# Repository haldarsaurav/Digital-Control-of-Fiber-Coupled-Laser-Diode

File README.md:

# Digital Control of Fiber Coupled Laser Diode

Developing a new digital circuit using a micro-controller to drive Laser (LED1) replacing analog methods of curent control. 

The Existing circuit we are trying to reeplicate digitally: 

Some of our objectives :- 

<ul>
  <li>Controlling the current to a LASER thorugh digital means instead of  analog means (Variable Resistors)</li>
  <li>Reading the current drawn and power of the LASER dynamicvally using INA219 Current Sensor</li>
  <li>Interfacing an LCD to monitor the display the PWM value of micro-controller and the curreent and poweer drawn dynamically</li>
</ul>  

Additional improvent and additions

<ul>
  <li>Adding a temperature sensor to measure the ambient temperature</li>
  <li>Adding a bluetooth transreciever to control the curreent value remotely</li> 
  <li>Developing an app or webpage based GUI application</li>
  <li>Logging all the data recieved and store it on sd card or cloud</li>
  <li>Housing all the electronics in a approprite housing.</li>
</ul>  

## Prototyping the existing circuit

Made the circuit following the schematic to drive the LASER

code snippet of sending increased PWM signals through A9 pin of Arduino 

    void loop() {
         analogWrite(9,100);                                           // Laser diode connected to pin A9
         delay(1000);
         analogWrite(9,150);
         delay(1000);
         analogWrite(9,200);
         delay(1000);
         analogWrite(9,250);
         delay(1000);
         analogWrite(9,0);
         delay(1000);
    }

## Intefaced the LCD to show any required data

Code with LCD initialsed:

    // include the library code:

    #include <LiquidCrystal.h>                                     // initialize the library by associating any needed LCD interface pin

    const int rs = 12, en = 11, d4 = 5, d5 = 4, d6 = 3, d7 = 2;    // with the arduino pin number it is connected to

    LiquidCrystal lcd(rs, en, d4, d5, d6, d7);

    void setup() {                                                 // set up the LCD's number of columns and rows:

    lcd.begin(16, 2);

    }

    void loop() {
     analogWrite(9,100);                                           // Laser diode connected to pin A9
     delay(1000);
     analogWrite(9,150);
     delay(1000);
     analogWrite(9,200);
     delay(1000);
     analogWrite(9,250);
     delay(1000);
     analogWrite(9,0);
     delay(1000);

                                                               // LCD Message
    lcd.print("   HELLO       ");
    lcd.setCursor(0,1);                                        // Set the cursor for the second line( the second 1 after comma sets the cursor at the 2 or lower line).
    lcd.print("      WORLD "); 

    }

## Interfaced the INA219 Current sensor to measure the current value

The vale from the INA219 using the LCD's LED as load :) (As I am doing this project Hochschule, I am quite restricted with parts)

Code for inteerfacing INA219 and measuring the current values

    #include <Wire.h>
    #include <Adafruit_INA219.h>

    Adafruit_INA219 ina219;

    void setup(void) 
    {
      Serial.begin(9600);
      while (!Serial) {
          // will pause Zero, Leonardo, etc until serial console opens
          delay(1);
      }

      uint32_t currentFrequency;

      Serial.println("Hello!");

      if (! ina219.begin()) {
        Serial.println("Failed to find INA219 chip");
        while (1) { delay(10); }
      }

      Serial.println("Measuring voltage and current with INA219 ...");
    }

    void loop(void) 
    {
      float shuntvoltage = 0;
      float busvoltage = 0;
      float current_mA = 0;
      float loadvoltage = 0;
      float power_mW = 0;

      shuntvoltage = ina219.getShuntVoltage_mV();
      busvoltage = ina219.getBusVoltage_V();
      current_mA = ina219.getCurrent_mA();
      power_mW = ina219.getPower_mW();
      loadvoltage = busvoltage + (shuntvoltage / 1000);

      Serial.print("Bus Voltage:   "); Serial.print(busvoltage); Serial.println(" V");
      Serial.print("Shunt Voltage: "); Serial.print(shuntvoltage); Serial.println(" mV");
      Serial.print("Load Voltage:  "); Serial.print(loadvoltage); Serial.println(" V");
      Serial.print("Current:       "); Serial.print(current_mA); Serial.println(" mA");
      Serial.print("Power:         "); Serial.print(power_mW); Serial.println(" mW");
      Serial.println("");

      delay(2000);
    }

Schematic for the entire plan and existing circuits which are already implemented, we can futher make the system more compact using an on-board ATMEGA328 IC.

We plan to use MCP4725 to convert the analog PWM signals from Arduino to digital values then use that to drive a current controlled Op-amp circuit in a voltage followeer mode. 

Some of my simulations :-

and then use a HM10 Blueetooth module to control the system oveer bluetooth remotely.

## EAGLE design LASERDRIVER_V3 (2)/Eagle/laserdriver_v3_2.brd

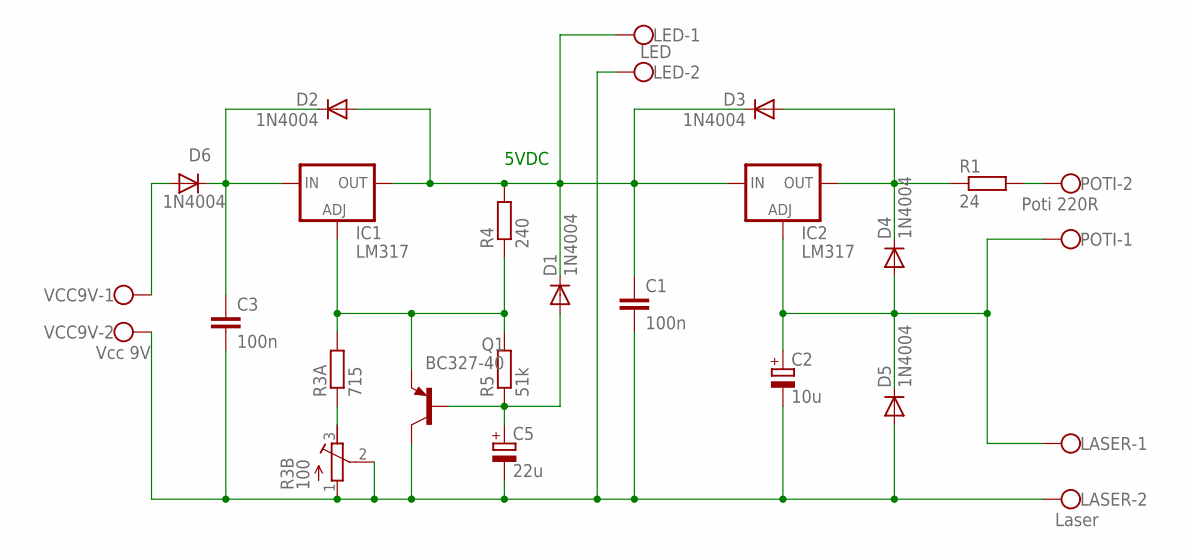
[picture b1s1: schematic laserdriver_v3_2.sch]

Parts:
C1, C3: 100n; C050-024X044
C2: 10u; E2-5
C5: 22u; E2-5
D1, D2, D3, D4, D5, D6: 1N4004; DO41-10
IC1, IC2: LM317; 317TS
LASER: Laser; W237-102
LED: LED; W237-102
POTI: Poti 220R; W237-102
Q1: BC327-40; TO92-EBC
R1: 24; 0207/7
R3A: 715; 0207/7
R3B: 100; RTRIM3296W
R4: 240; 0207/7
R5: 51k; 0207/7
VCC9V: Vcc 9V; W237-102

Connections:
unnamed: C1.1, D1.C, D2.A, D3.C, IC1.2 (OUT), IC2.3 (IN), LED.1, R4.2
unnamed: C2.+, D4.A, D5.C, IC2.1 (ADJ), LASER.1, POTI.1
unnamed: D3.A, D4.C, IC2.2 (OUT), R1.1
unnamed: POTI.2, R1.2
unnamed: C5.+, D1.A, Q1.B, R5.1
unnamed: D6.A, VCC9V.1
unnamed: C3.1, D2.C, D6.C, IC1.3 (IN)
unnamed: R3A.1, R3B.3 (E)
unnamed: C1.2, C2.-, C3.2, C5.-, D5.A, LASER.2, LED.2, Q1.C, R3B.1 (A), R3B.2 (S), VCC9V.2
unnamed: IC1.1 (ADJ), Q1.E, R3A.2, R4.1, R5.2

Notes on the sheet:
5VDC

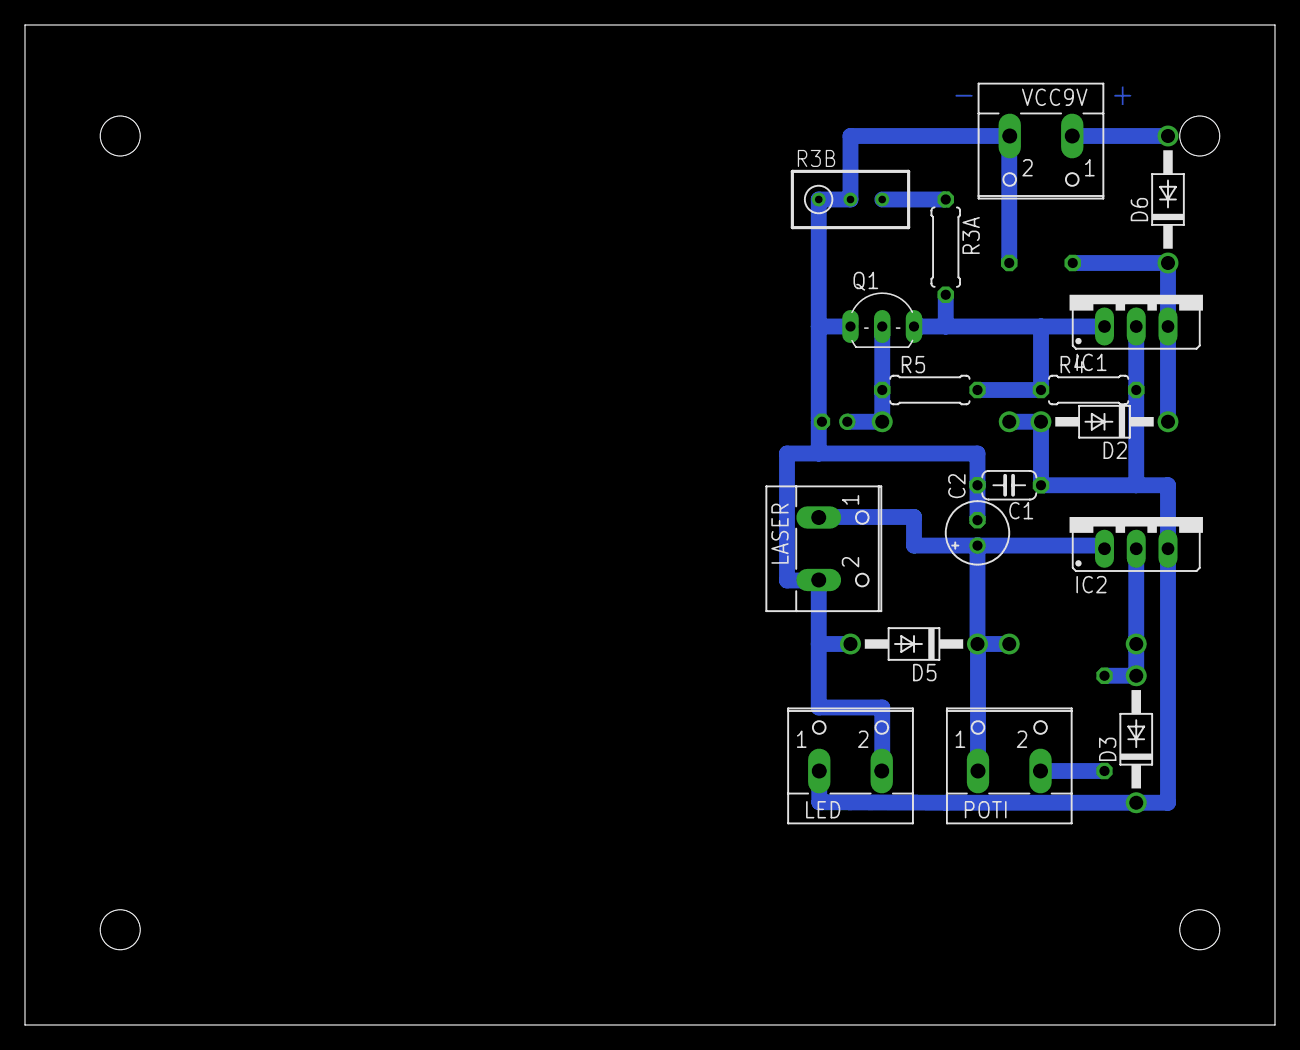
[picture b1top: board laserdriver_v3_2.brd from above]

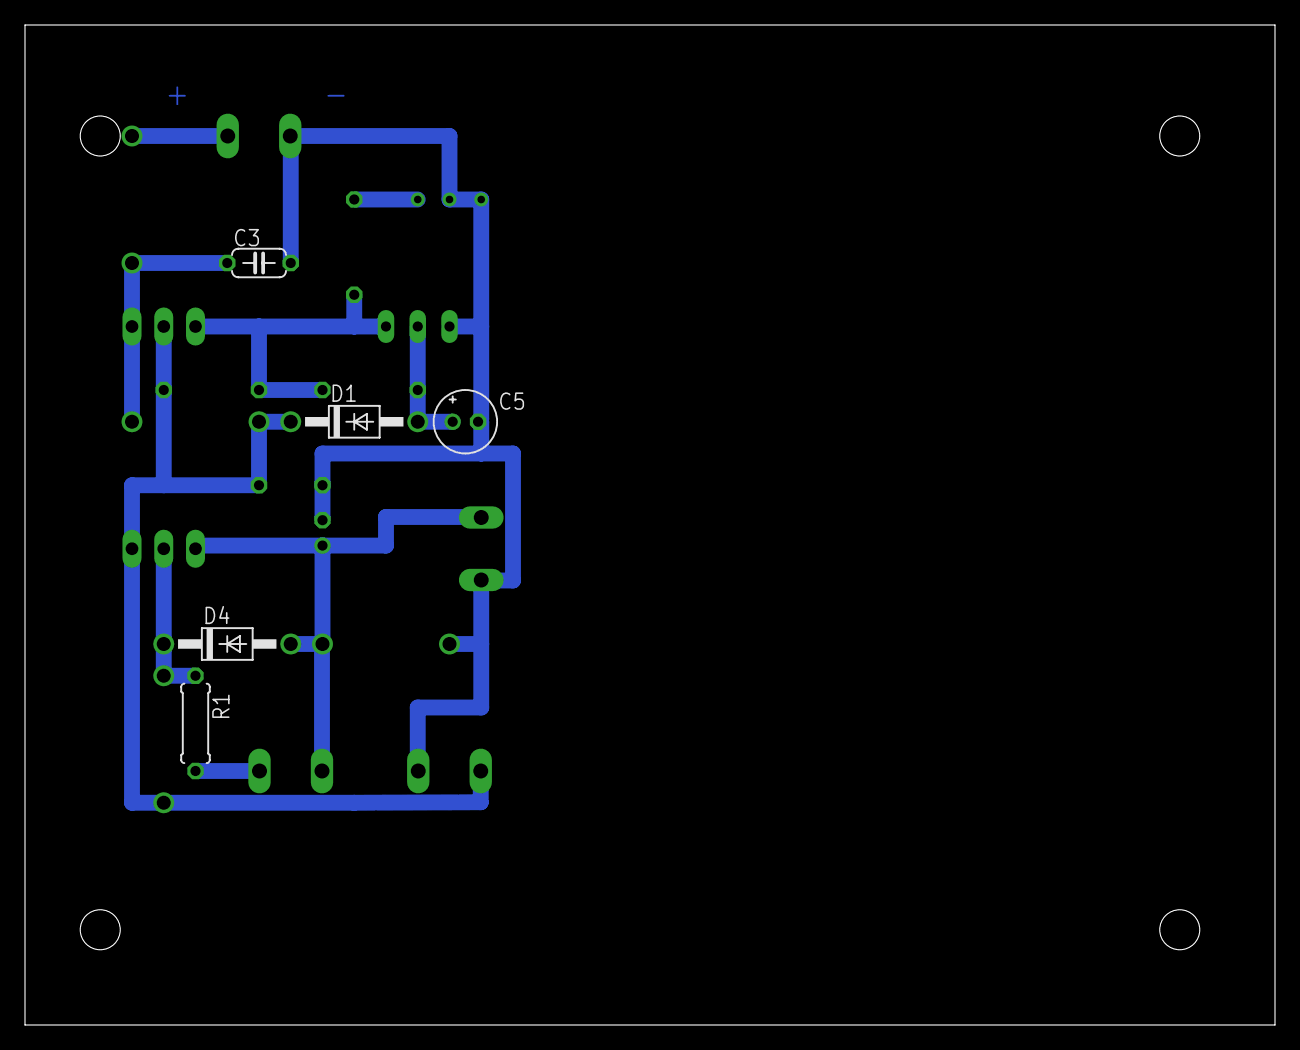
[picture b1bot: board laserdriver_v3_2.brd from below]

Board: 2 copper layers, 100.0 x 80.0 mm, 22 parts (5 on the bottom side), 10 nets.

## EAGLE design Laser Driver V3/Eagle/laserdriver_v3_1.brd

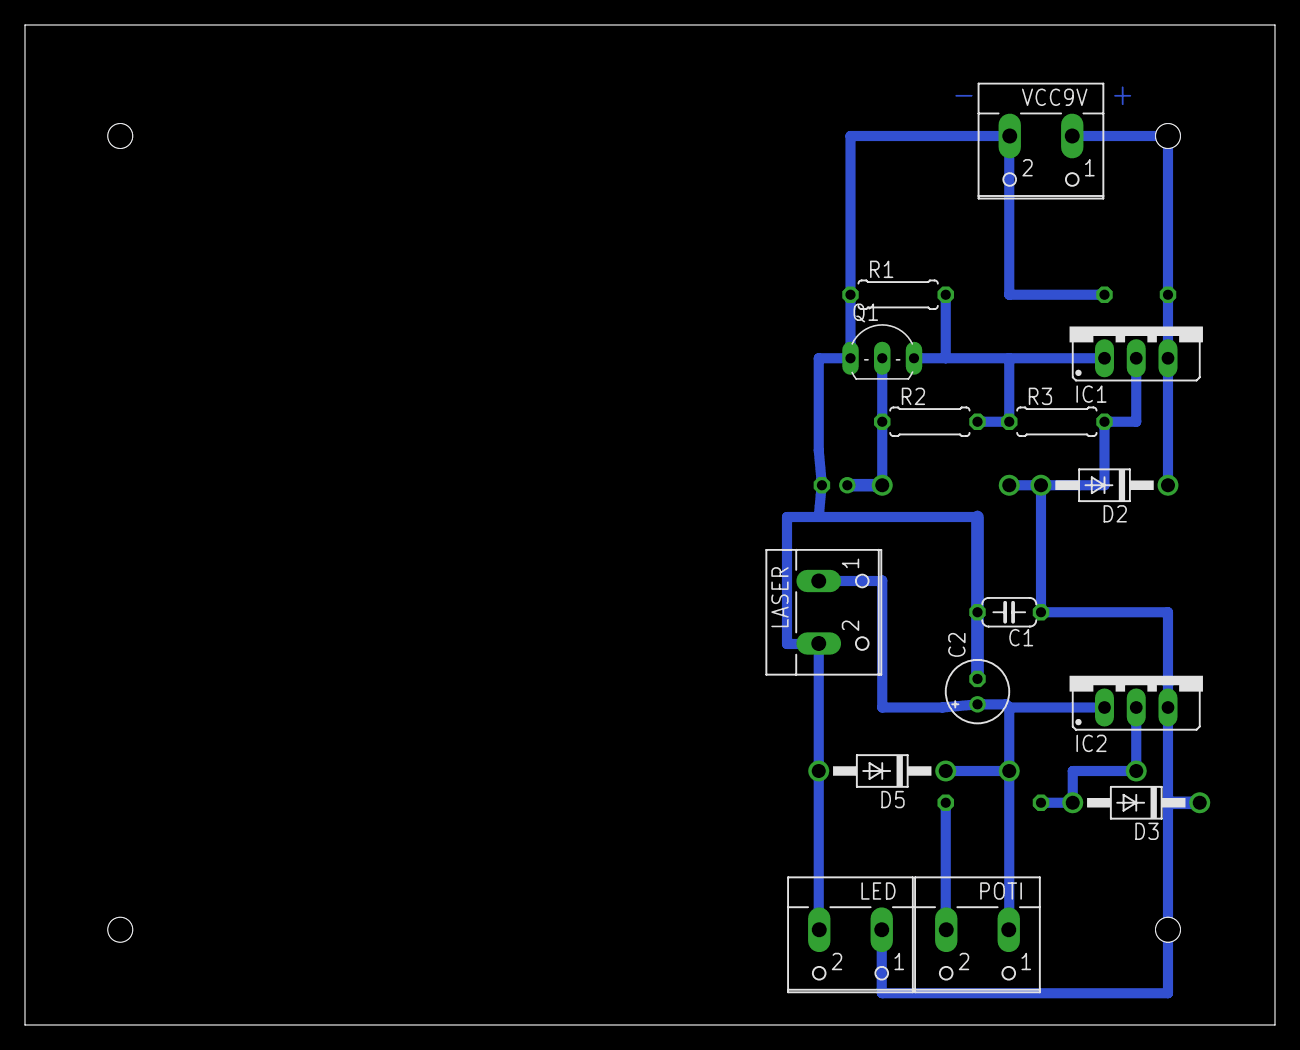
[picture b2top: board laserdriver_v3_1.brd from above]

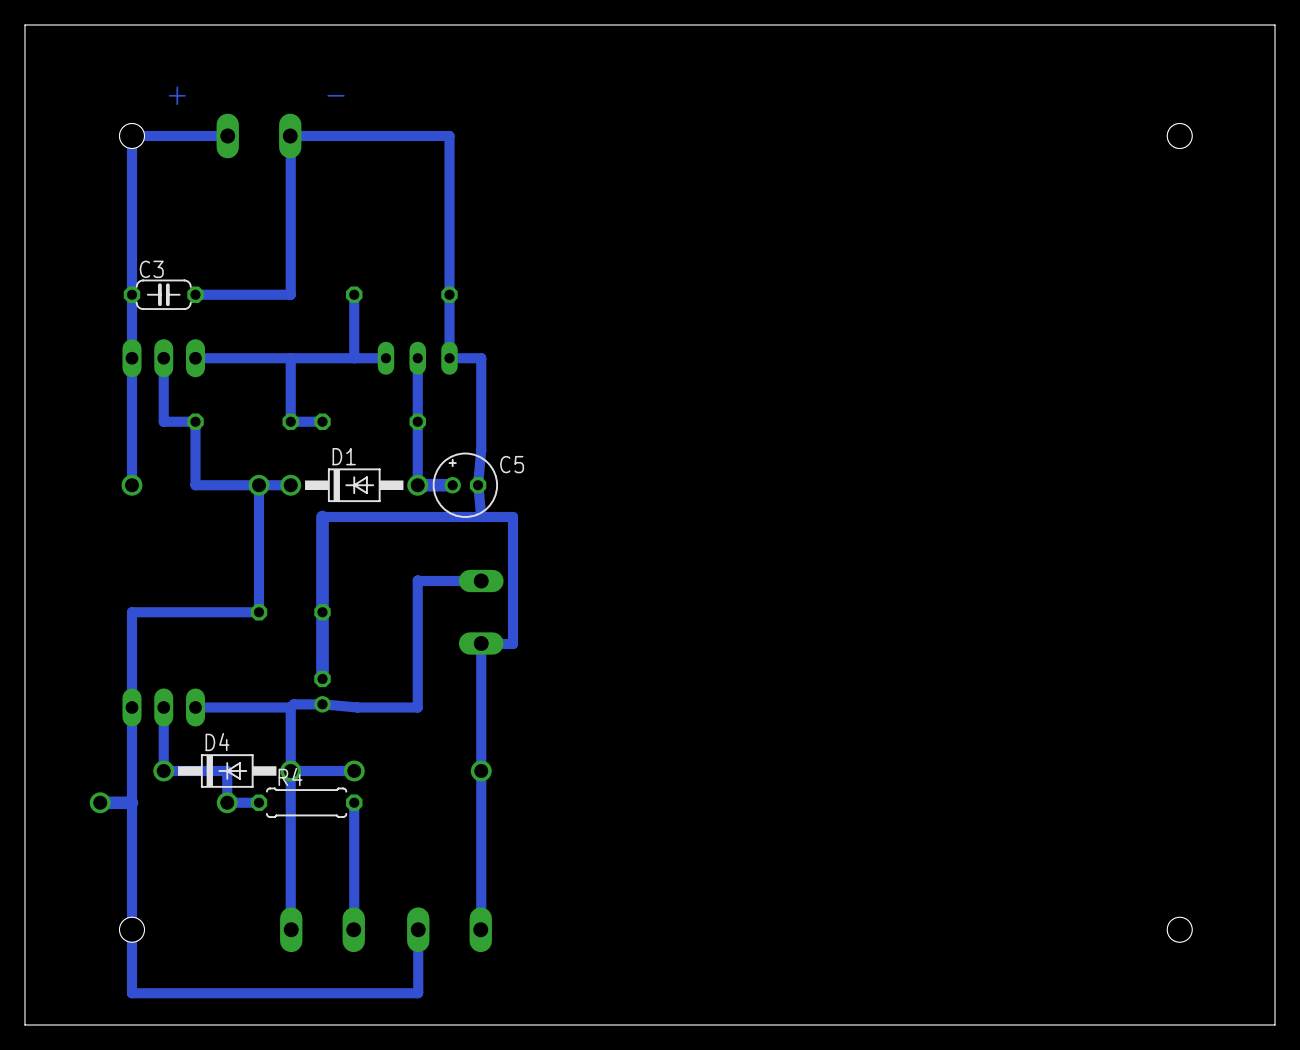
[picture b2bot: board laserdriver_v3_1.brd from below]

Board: 2 copper layers, 100.0 x 80.0 mm, 20 parts (5 on the bottom side), 8 nets.

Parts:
C1, C3: 100n; C050-024X044
C2: 10u; E2-5
C5: 22u; E2-5
D1, D2, D3, D4, D5: 1N4004; DO41-10
IC1, IC2: LM317; 317TS
LASER: Laser; W237-102
LED: LED; W237-102
POTI: Poti 220R; W237-102
Q1: BC327-40; TO92-EBC
R1: 720; 0207/7
R2: 50k; 0207/7
R3: 240; 0207/7
R4: 24; 0207/7
VCC9V: Vcc 9V; W237-102

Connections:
unnamed: C1.1, D1.C, D2.A, D3.C, IC1.2, IC2.3, LED.1, R3.2
unnamed: C2.+, D4.A, D5.C, IC2.1, LASER.1, POTI.1
unnamed: D3.A, D4.C, IC2.2, R4.1
unnamed: POTI.2, R4.2
unnamed: C5.+, D1.A, Q1.B, R2.1
unnamed: C3.1, D2.C, IC1.3, VCC9V.1
unnamed: C1.2, C2.-, C3.2, C5.-, D5.A, LASER.2, LED.2, Q1.C, R1.1, VCC9V.2
unnamed: IC1.1, Q1.E, R1.2, R2.2, R3.1

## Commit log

2022-06-23 added the files
2022-06-23 added psuedo code
2022-06-23 some rearrangements
2022-06-24 changes to code
2022-06-24 add spaces \
2022-06-24 initialised LCD
2022-06-24 initiliased LCD
2022-06-24 added LCD
2022-06-25 added current sensor code
2022-06-25 init
2022-06-25 added images
2022-06-26 deleted some images
2022-06-26 renamed file
2022-06-26 folder rearranged
2022-06-26 new code
2022-06-26 code serial baud rate
2022-06-26 ranem
2022-06-26 added libraries
2022-06-26 added datasheet
2022-07-29 added new images
2022-07-29 addeed pic
2022-07-29 added pics of existing circuit
2022-07-29 rearranged some pics
2022-07-29 added schematic pdf
2022-07-29 added simulations
2022-07-29 image resize
